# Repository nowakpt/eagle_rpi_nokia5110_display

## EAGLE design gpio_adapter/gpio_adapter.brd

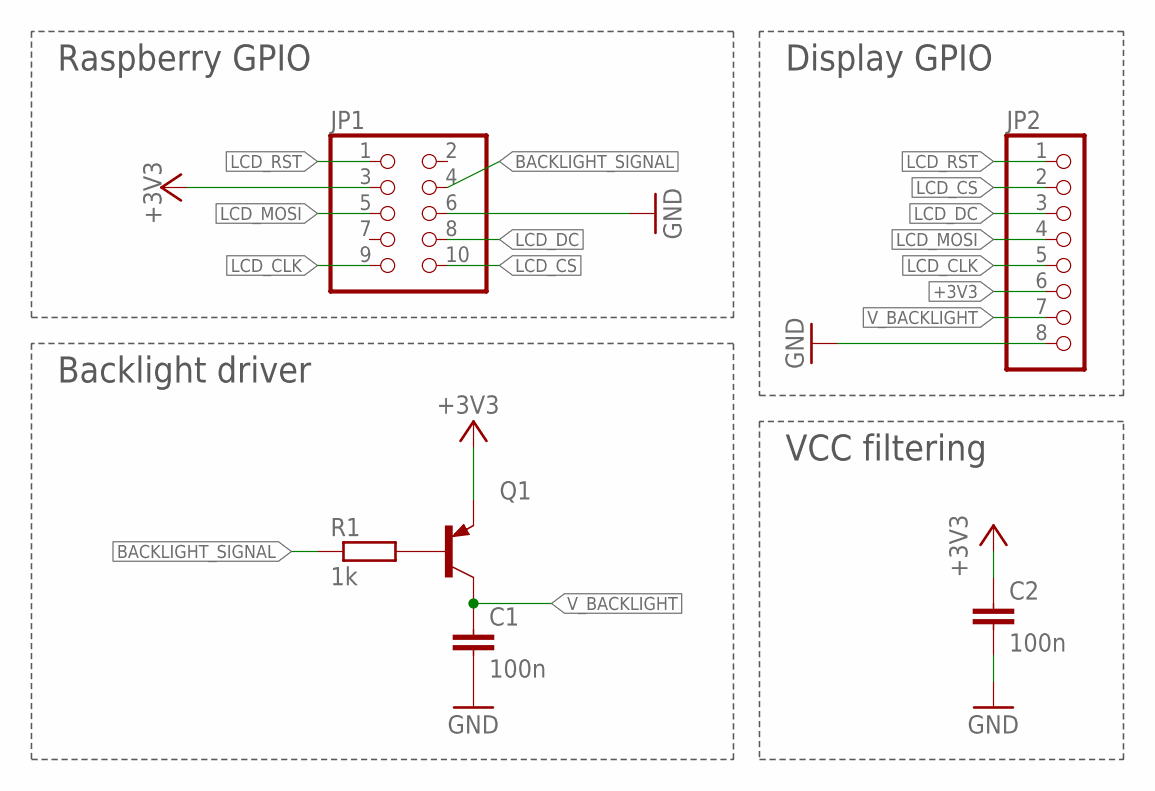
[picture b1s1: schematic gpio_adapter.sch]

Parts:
C1, C2: 100n; C0805
JP1: PINHD-2X5; 2X05
JP2: PINHD-1X8/90; 1X08/90
Q1: BC807-40SMD; SOT23-BEC
R1: 1k; R0805

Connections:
+3V3: C2.1, JP1.3, JP2.6, Q1.E
BACKLIGHT_SIGNAL: JP1.4, R1.1
GND: C1.2, C2.2, JP1.6, JP2.8
LCD_CLK: JP1.9, JP2.5
LCD_CS: JP1.10, JP2.2
LCD_DC: JP1.8, JP2.3
LCD_MOSI: JP1.5, JP2.4
LCD_RST: JP1.1, JP2.1
unnamed: Q1.B, R1.2
V_BACKLIGHT: C1.1, JP2.7, Q1.C

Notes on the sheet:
Raspberry GPIO
Display GPIO
Backlight driver
VCC filtering

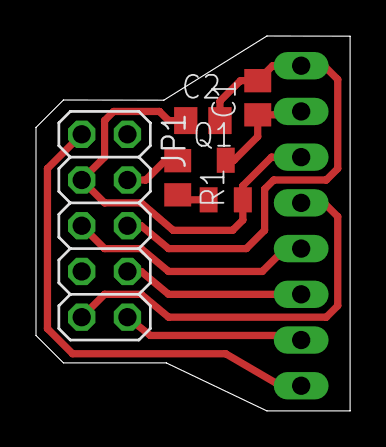
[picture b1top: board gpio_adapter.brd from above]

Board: 2 copper layers, 17.4 x 20.8 mm, 6 parts (1 on the bottom side), 10 nets.

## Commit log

2015-08-06 updated .gitignore: ignoring auto-backup files
2015-08-06 added adapter schematic
2015-08-06 corrected schematic, added board design
2015-08-07 modified board: size optimization
